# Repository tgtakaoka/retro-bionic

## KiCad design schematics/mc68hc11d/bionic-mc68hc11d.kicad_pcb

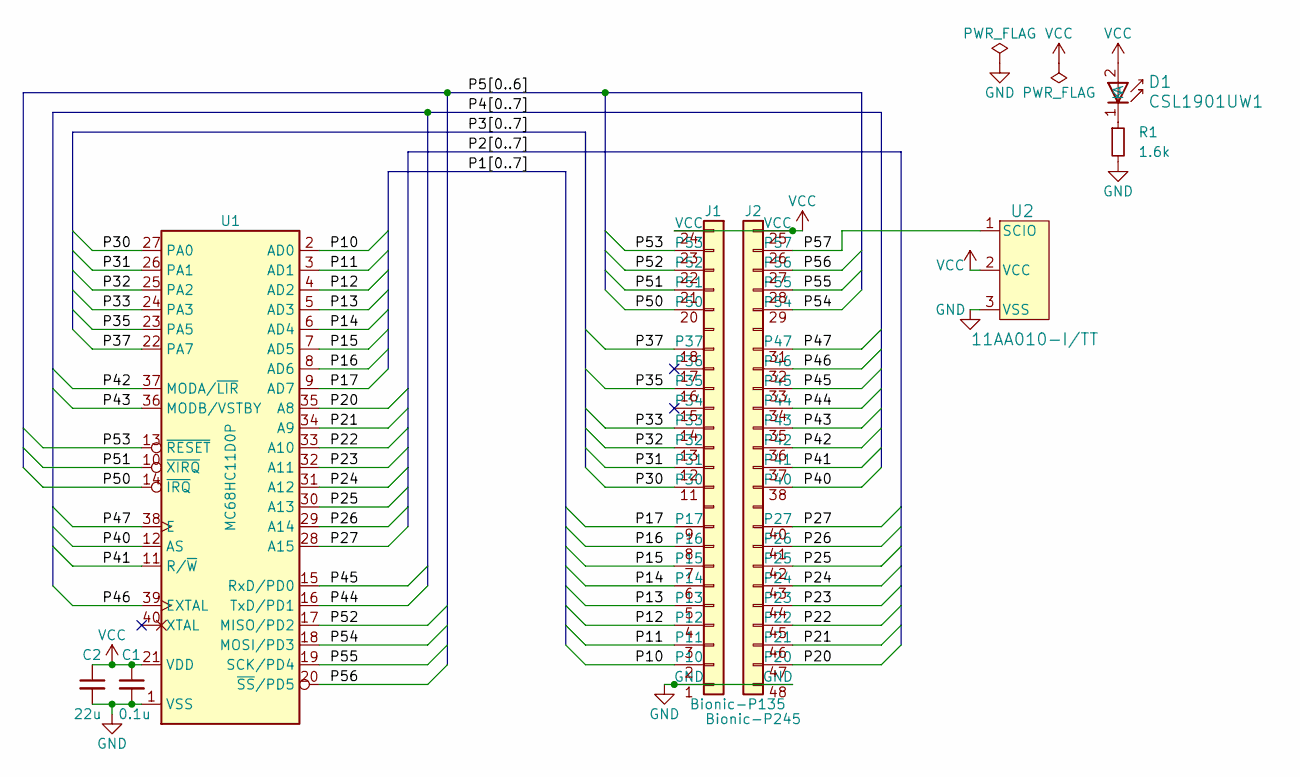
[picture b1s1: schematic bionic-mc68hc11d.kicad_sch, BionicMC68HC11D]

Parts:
C1: 0.1u; C_0603_1608Metric_Pad1.08x0.95mm_HandSolder
C2: 22u; C_0603_1608Metric_Pad1.08x0.95mm_HandSolder
D1: CSL1901UW1; LED_CSL1901UW1_ROM-M
J1: Bionic-P135; Bionic-P135_THT
J2: Bionic-P245; Bionic-P245_THT
R1: 1.6k; R_0603_1608Metric_Pad0.98x0.95mm_HandSolder
U1: MC68HC11D0P; DIP-40_W15.24mm_Socket
U2: 11AA010-I/TT; SOT-23_MC_MCH-M

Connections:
/P10: J1.2 (P10), U1.2 (AD0)
/P11: J1.3 (P11), U1.3 (AD1)
/P12: J1.4 (P12), U1.4 (AD2)
/P13: J1.5 (P13), U1.5 (AD3)
/P14: J1.6 (P14), U1.6 (AD4)
/P15: J1.7 (P15), U1.7 (AD5)
/P16: J1.8 (P16), U1.8 (AD6)
/P17: J1.9 (P17), U1.9 (AD7)
/P20: J2.47 (P20), U1.35 (A8)
/P21: J2.46 (P21), U1.34 (A9)
/P22: J2.45 (P22), U1.33 (A10)
/P23: J2.44 (P23), U1.32 (A11)
/P24: J2.43 (P24), U1.31 (A12)
/P25: J2.42 (P25), U1.30 (A13)
/P26: J2.41 (P26), U1.29 (A14)
/P27: J2.40 (P27), U1.28 (A15)
/P30: J1.11 (P30), U1.27 (PA0)
/P31: J1.12 (P31), U1.26 (PA1)
/P32: J1.13 (P32), U1.25 (PA2)
/P33: J1.14 (P33), U1.24 (PA3)
/P35: J1.16 (P35), U1.23 (PA5)
/P37: J1.18 (P37), U1.22 (PA7)
/P40: J2.38 (P40), U1.12 (AS)
/P41: J2.37 (P41), U1.11 (R/~W)
/P42: J2.36 (P42), U1.37 (MODA/~LIR)
/P43: J2.35 (P43), U1.36 (MODB/VSTBY)
/P44: J2.34 (P44), U1.16 (TxD/PD1)
/P45: J2.33 (P45), U1.15 (RxD/PD0)
/P46: J2.32 (P46), U1.39 (EXTAL)
/P47: J2.31 (P47), U1.38 (E)
/P50: J1.20 (P50), U1.14 (~IRQ)
/P51: J1.21 (P51), U1.10 (~XIRQ)
/P52: J1.22 (P52), U1.17 (MISO/PD2)
/P53: J1.23 (P53), U1.13 (~RESET)
/P54: J2.29 (P54), U1.18 (MOSI/PD3)
/P55: J2.28 (P55), U1.19 (SCK/PD4)
/P56: J2.27 (P56), U1.20 (~SS/PD5)
/P57: J2.26 (P57), U2.1 (SCIO)
GND: C1.2, C2.2, J1.1 (GND), J2.48 (GND), R1.2, U1.1 (VSS), U2.3 (VSS)
unnamed: D1.1 (K), R1.1
VCC: C1.1, C2.1, D1.2 (A), J1.24 (VCC), J2.25 (VCC), U1.21 (VDD), U2.2 (VCC)

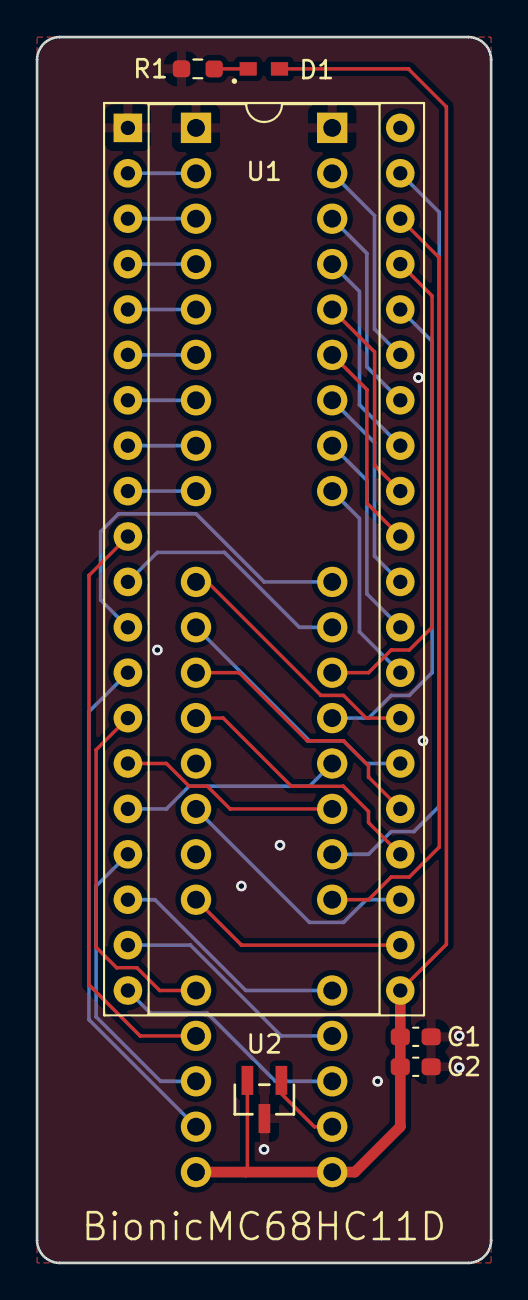
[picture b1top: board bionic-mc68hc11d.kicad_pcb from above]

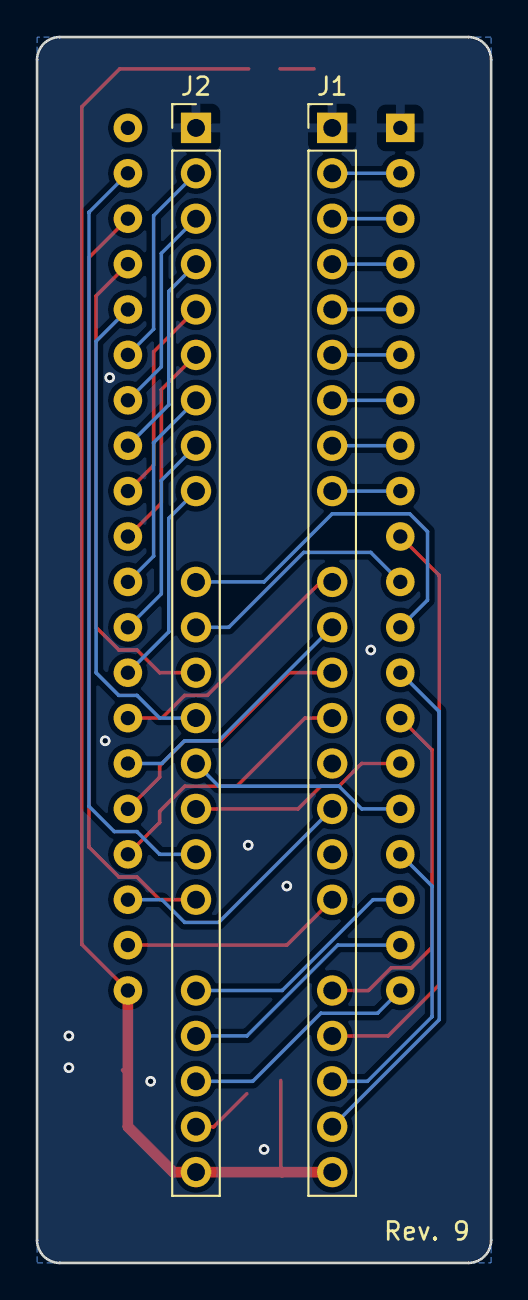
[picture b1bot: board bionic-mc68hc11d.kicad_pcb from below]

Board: 2 copper layers, 25.4 x 68.6 mm, 8 parts (2 on the bottom side), 41 nets.

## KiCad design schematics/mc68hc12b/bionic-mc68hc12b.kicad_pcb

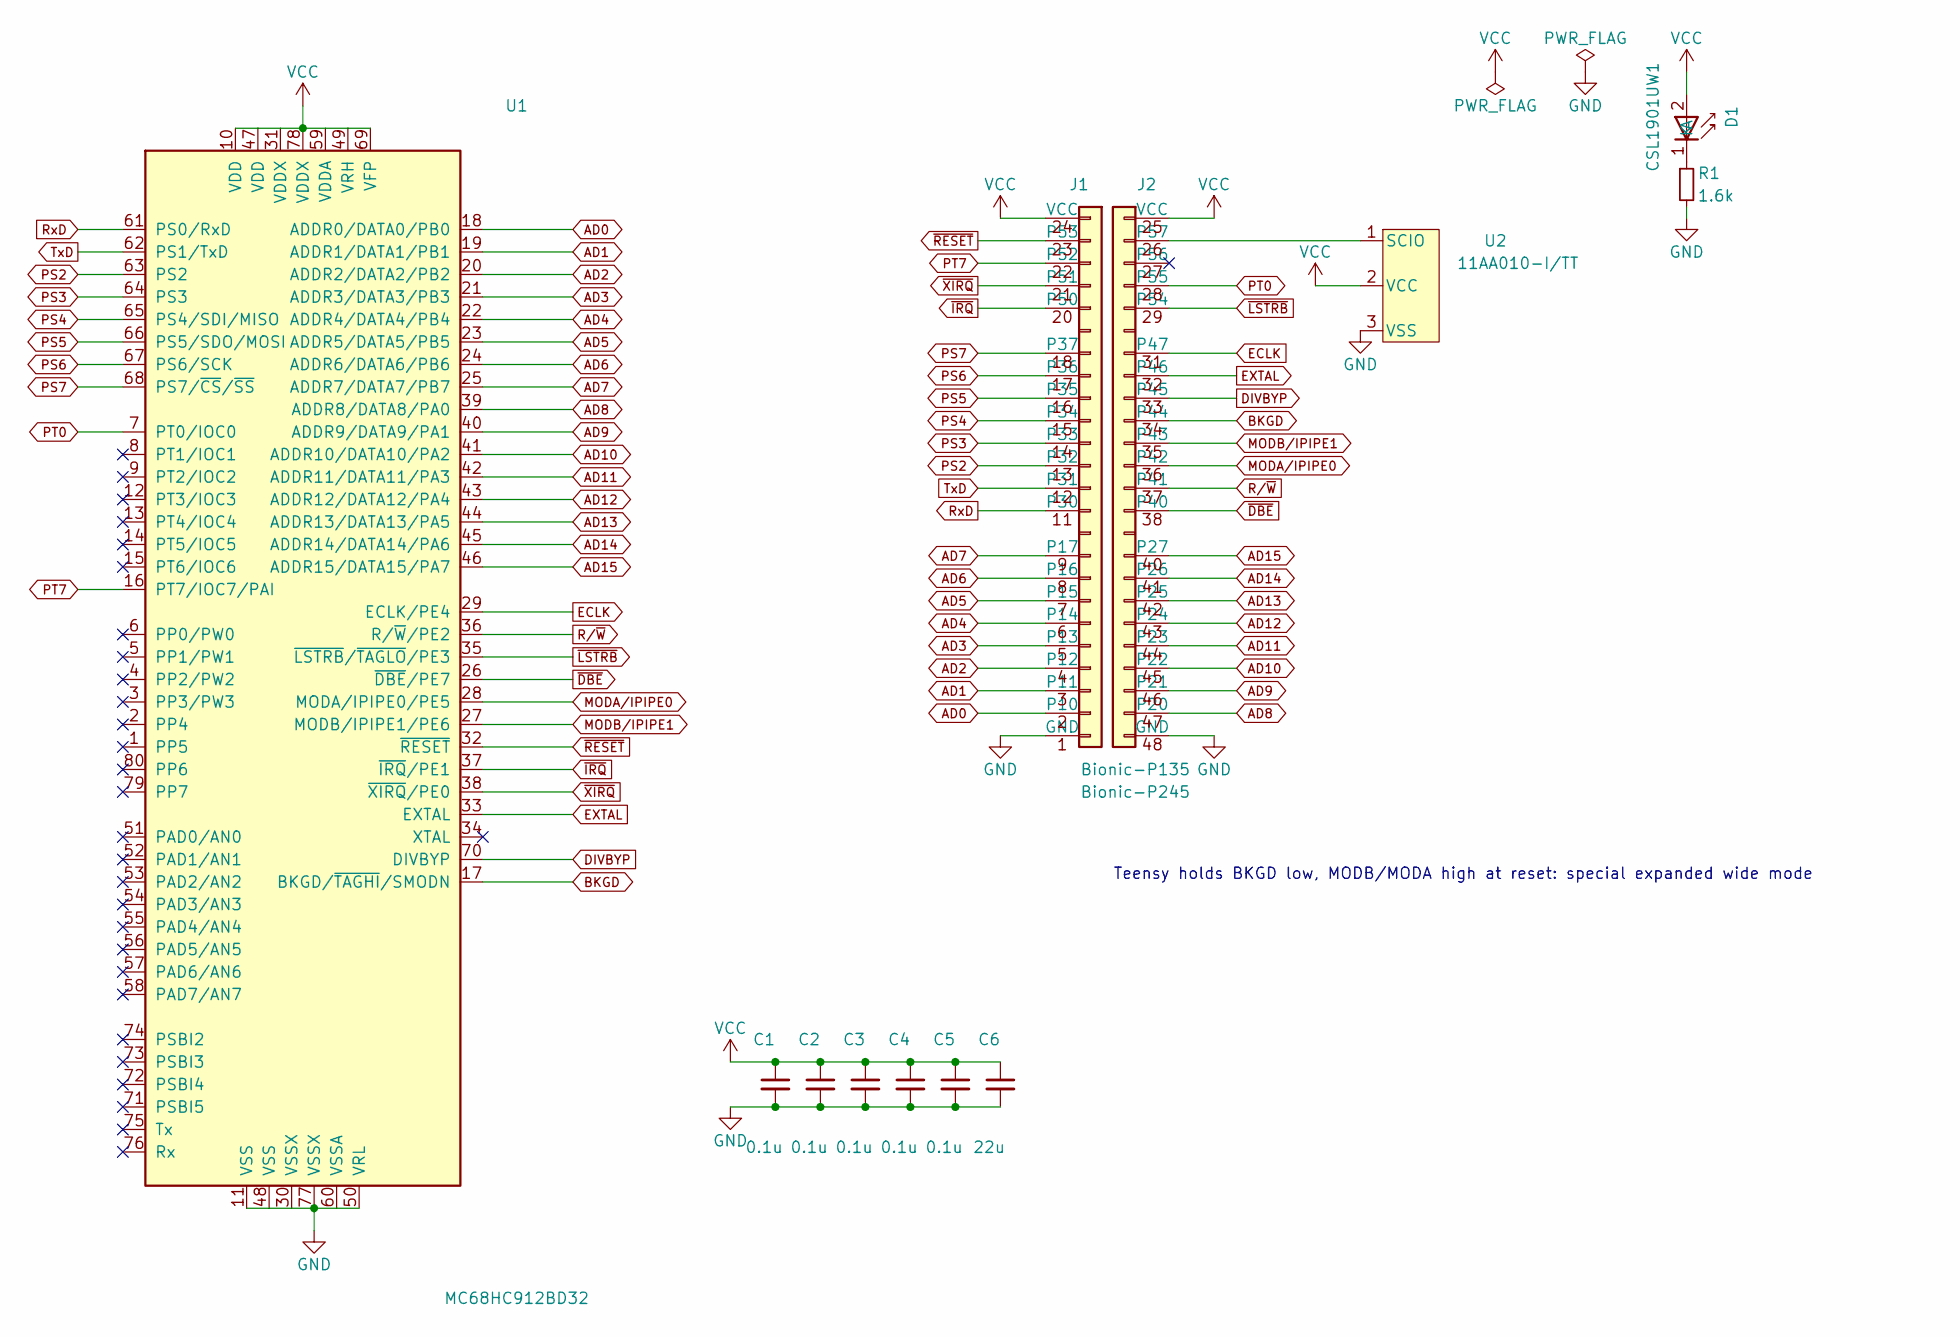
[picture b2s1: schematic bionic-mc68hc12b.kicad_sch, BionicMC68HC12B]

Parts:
C1, C2, C3, C4, C5: 0.1u; C_0603_1608Metric_Pad1.08x0.95mm_HandSolder
C6: 22u; C_0603_1608Metric_Pad1.08x0.95mm_HandSolder
D1: CSL1901UW1; LED_CSL1901UW1_ROM-M
J1: Bionic-P135; Bionic-P135_SMT
J2: Bionic-P245; Bionic-P245_SMT
R1: 1.6k; R_0603_1608Metric_Pad0.98x0.95mm_HandSolder
U1: MC68HC912BD32; PQFP-80_14x14mm_P0.65mm
U2: 11AA010-I/TT; SOT-23_MC_MCH-M

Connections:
AD0: J1.2 (P10), U1.18 (ADDR0/DATA0/PB0)
AD1: J1.3 (P11), U1.19 (ADDR1/DATA1/PB1)
AD2: J1.4 (P12), U1.20 (ADDR2/DATA2/PB2)
AD3: J1.5 (P13), U1.21 (ADDR3/DATA3/PB3)
AD4: J1.6 (P14), U1.22 (ADDR4/DATA4/PB4)
AD5: J1.7 (P15), U1.23 (ADDR5/DATA5/PB5)
AD6: J1.8 (P16), U1.24 (ADDR6/DATA6/PB6)
AD7: J1.9 (P17), U1.25 (ADDR7/DATA7/PB7)
AD8: J2.47 (P20), U1.39 (ADDR8/DATA8/PA0)
AD9: J2.46 (P21), U1.40 (ADDR9/DATA9/PA1)
AD10: J2.45 (P22), U1.41 (ADDR10/DATA10/PA2)
AD11: J2.44 (P23), U1.42 (ADDR11/DATA11/PA3)
AD12: J2.43 (P24), U1.43 (ADDR12/DATA12/PA4)
AD13: J2.42 (P25), U1.44 (ADDR13/DATA13/PA5)
AD14: J2.41 (P26), U1.45 (ADDR14/DATA14/PA6)
AD15: J2.40 (P27), U1.46 (ADDR15/DATA15/PA7)
BKGD: J2.34 (P44), U1.17 (BKGD/~TAGHI/SMODN)
DIVBYP: J2.33 (P45), U1.70 (DIVBYP)
ECLK: J2.31 (P47), U1.29 (ECLK/PE4)
EXTAL: J2.32 (P46), U1.33 (EXTAL)
GND: C1.2, C2.2, C3.2, C4.2, C5.2, C6.2, J1.1 (GND), J2.48 (GND), R1.2, U1.11 (VSS), U1.30 (VSSX), U1.48 (VSS), U1.50 (VRL), U1.60 (VSSA), U1.77 (VSSX), U2.3 (VSS)
MODA/IPIPE0: J2.36 (P42), U1.28 (MODA/IPIPE0/PE5)
MODB/IPIPE1: J2.35 (P43), U1.27 (MODB/IPIPE1/PE6)
unnamed: D1.1 (K), R1.1
unnamed: J2.26 (P57), U2.1 (SCIO)
PS2: J1.13 (P32), U1.63 (PS2)
PS3: J1.14 (P33), U1.64 (PS3)
PS4: J1.15 (P34), U1.65 (PS4/SDI/MISO)
PS5: J1.16 (P35), U1.66 (PS5/SDO/MOSI)
PS6: J1.17 (P36), U1.67 (PS6/SCK)
PS7: J1.18 (P37), U1.68 (PS7/~CS/~SS)
PT0: J2.28 (P55), U1.7 (PT0/IOC0)
PT7: J1.22 (P52), U1.16 (PT7/IOC7/PAI)
RxD: J1.11 (P30), U1.61 (PS0/RxD)
R/~W: J2.37 (P41), U1.36 (R/~W/PE2)
TxD: J1.12 (P31), U1.62 (PS1/TxD)
VCC: C1.1, C2.1, C3.1, C4.1, C5.1, C6.1, D1.2 (A), J1.24 (VCC), J2.25 (VCC), U1.10 (VDD), U1.31 (VDDX), U1.47 (VDD), U1.49 (VRH), U1.59 (VDDA), U1.69 (VFP), U1.78 (VDDX), U2.2 (VCC)
~DBE: J2.38 (P40), U1.26 (~DBE/PE7)
~IRQ: J1.20 (P50), U1.37 (~IRQ/PE1)
~LSTRB: J2.29 (P54), U1.35 (~LSTRB/~TAGLO/PE3)
~RESET: J1.23 (P53), U1.32 (~RESET)
~XIRQ: J1.21 (P51), U1.38 (~XIRQ/PE0)

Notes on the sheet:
Teensy holds BKGD low, MODB/MODA high at reset: special expanded wide mode

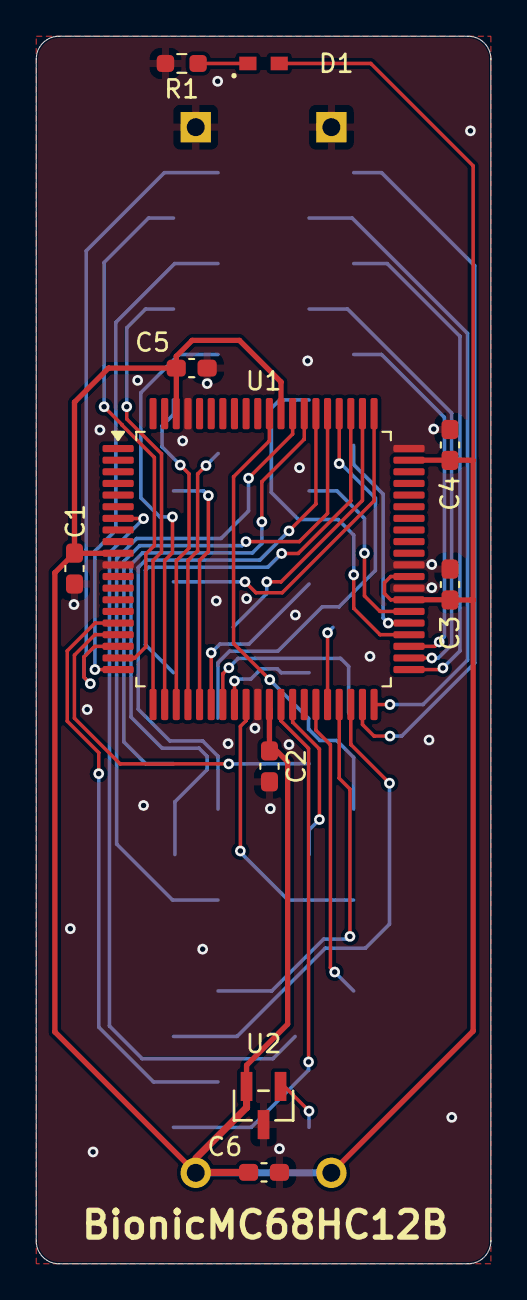
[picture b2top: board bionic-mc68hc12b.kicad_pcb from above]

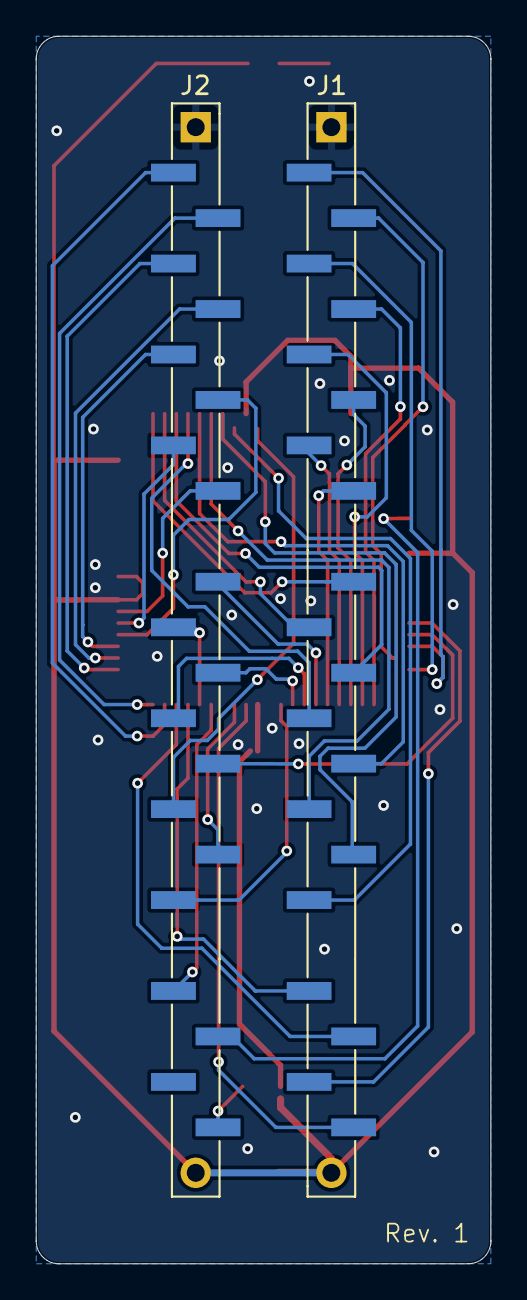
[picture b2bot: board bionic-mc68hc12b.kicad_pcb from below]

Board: 2 copper layers, 25.4 x 68.6 mm, 12 parts (2 on the bottom side), 42 nets.

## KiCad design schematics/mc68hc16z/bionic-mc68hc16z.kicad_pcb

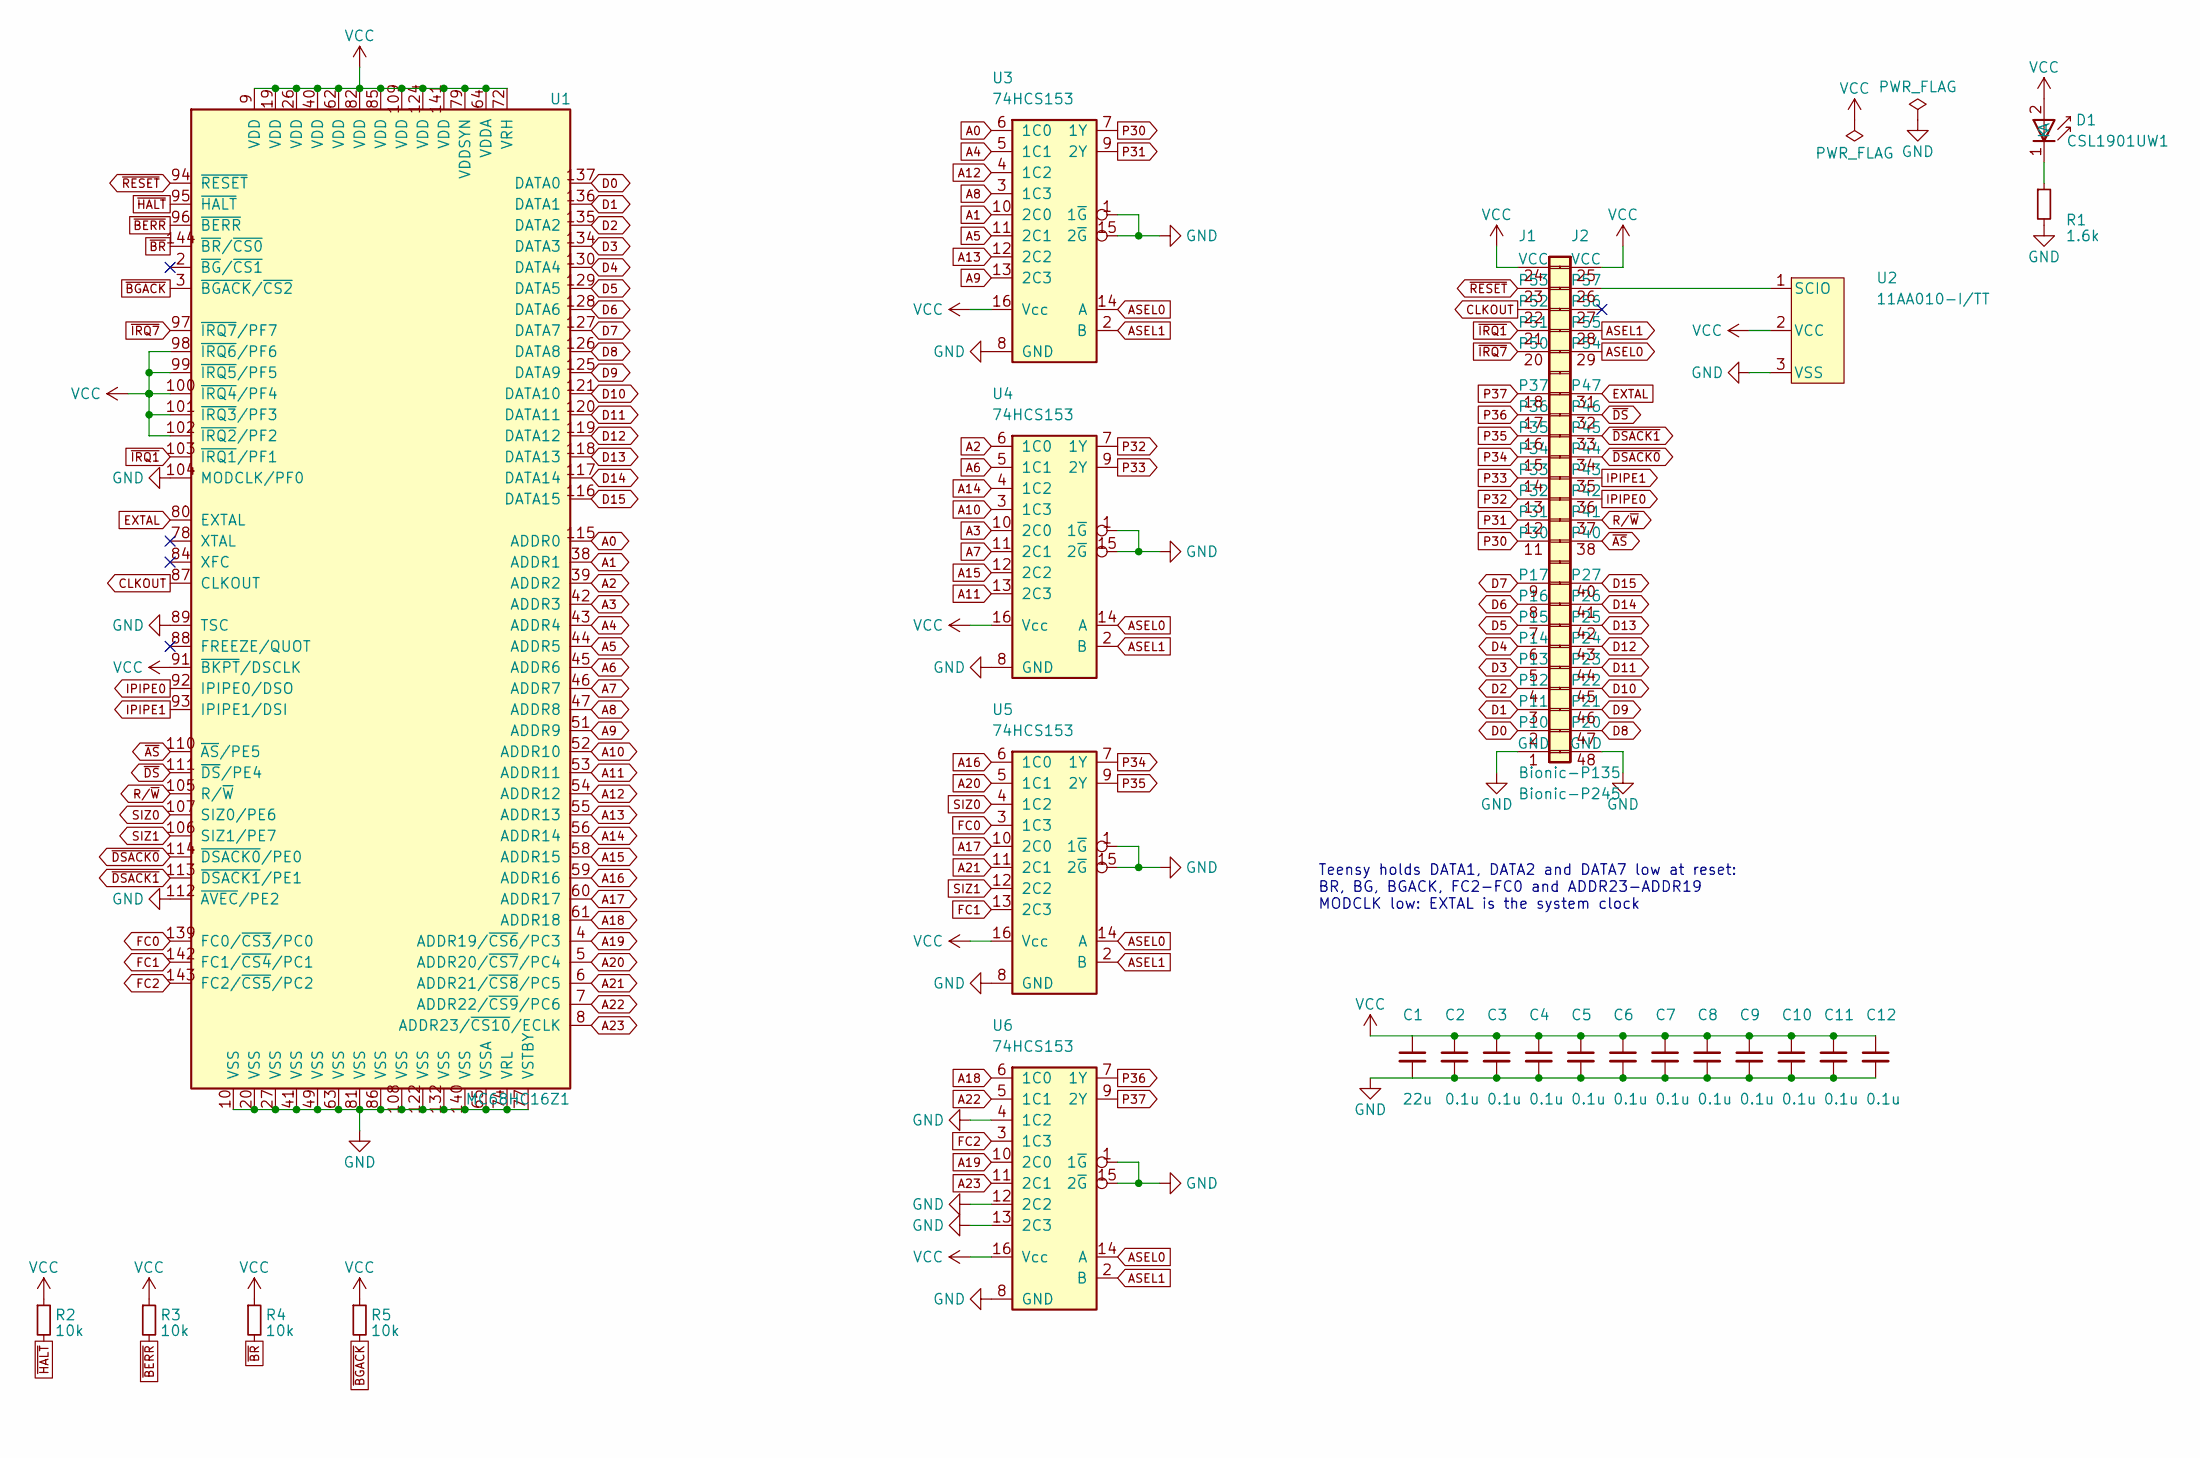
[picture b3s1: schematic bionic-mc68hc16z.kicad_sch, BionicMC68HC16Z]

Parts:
C1: 22u; C_0603_1608Metric_Pad1.08x0.95mm_HandSolder
C2, C3, C4, C5, C6, C7, C8, C9, C10, C11, C12: 0.1u; C_0603_1608Metric_Pad1.08x0.95mm_HandSolder
D1: CSL1901UW1; LED_CSL1901UW1_ROM-M
J1: Bionic-P135; Bionic-P135_SMT
J2: Bionic-P245; Bionic-P245_SMT
R1: 1.6k; R_0603_1608Metric_Pad0.98x0.95mm_HandSolder
R2, R3, R4, R5: 10k; R_0603_1608Metric_Pad0.98x0.95mm_HandSolder
U1: MC68HC16Z1; LQFP-144_20x20mm_P0.5mm
U2: 11AA010-I/TT; SOT-23_MC_MCH-M
U3, U4, U5, U6: 74HCS153; PW16-M

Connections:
A0: U1.115 (ADDR0), U3.6 (1C0)
A1: U1.38 (ADDR1), U3.10 (2C0)
A2: U1.39 (ADDR2), U4.6 (1C0)
A3: U1.42 (ADDR3), U4.10 (2C0)
A4: U1.43 (ADDR4), U3.5 (1C1)
A5: U1.44 (ADDR5), U3.11 (2C1)
A6: U1.45 (ADDR6), U4.5 (1C1)
A7: U1.46 (ADDR7), U4.11 (2C1)
A8: U1.47 (ADDR8), U3.3 (1C3)
A9: U1.51 (ADDR9), U3.13 (2C3)
A10: U1.52 (ADDR10), U4.3 (1C3)
A11: U1.53 (ADDR11), U4.13 (2C3)
A12: U1.54 (ADDR12), U3.4 (1C2)
A13: U1.55 (ADDR13), U3.12 (2C2)
A14: U1.56 (ADDR14), U4.4 (1C2)
A15: U1.58 (ADDR15), U4.12 (2C2)
A16: U1.59 (ADDR16), U5.6 (1C0)
A17: U1.60 (ADDR17), U5.10 (2C0)
A18: U1.61 (ADDR18), U6.6 (1C0)
A19: U1.4 (ADDR19/~CS6/PC3), U6.10 (2C0)
A20: U1.5 (ADDR20/~CS7/PC4), U5.5 (1C1)
A21: U1.6 (ADDR21/~CS8/PC5), U5.11 (2C1)
A22: U1.7 (ADDR22/~CS9/PC6), U6.5 (1C1)
A23: U1.8 (ADDR23/~CS10/ECLK), U6.11 (2C1)
ASEL0: J2.29 (P54), U3.14 (A), U4.14 (A), U5.14 (A), U6.14 (A)
ASEL1: J2.28 (P55), U3.2 (B), U4.2 (B), U5.2 (B), U6.2 (B)
CLKOUT: J1.22 (P52), U1.87 (CLKOUT)
D0: J1.2 (P10), U1.137 (DATA0)
D1: J1.3 (P11), U1.136 (DATA1)
D2: J1.4 (P12), U1.135 (DATA2)
D3: J1.5 (P13), U1.134 (DATA3)
D4: J1.6 (P14), U1.130 (DATA4)
D5: J1.7 (P15), U1.129 (DATA5)
D6: J1.8 (P16), U1.128 (DATA6)
D7: J1.9 (P17), U1.127 (DATA7)
D8: J2.47 (P20), U1.126 (DATA8)
D9: J2.46 (P21), U1.125 (DATA9)
D10: J2.45 (P22), U1.121 (DATA10)
D11: J2.44 (P23), U1.120 (DATA11)
D12: J2.43 (P24), U1.119 (DATA12)
D13: J2.42 (P25), U1.118 (DATA13)
D14: J2.41 (P26), U1.117 (DATA14)
D15: J2.40 (P27), U1.116 (DATA15)
EXTAL: J2.31 (P47), U1.80 (EXTAL)
FC0: U1.139 (FC0/~CS3/PC0), U5.3 (1C3)
FC1: U1.142 (FC1/~CS4/PC1), U5.13 (2C3)
FC2: U1.143 (FC2/~CS5/PC2), U6.3 (1C3)
GND: C1.2, C2.2, C3.2, C4.2, C5.2, C6.2, C7.2, C8.2, C9.2, C10.2, C11.2, C12.2, J1.1 (GND), J2.48 (GND), R1.2, U1.10 (VSS), U1.20 (VSS), U1.27 (VSS), U1.41 (VSS), U1.49 (VSS), U1.63 (VSS), U1.65 (VSSA), U1.74 (VRL), U1.77 (VSTBY), U1.81 (VSS), U1.86 (VSS), U1.89 (TSC), U1.104 (MODCLK/PF0), U1.108 (VSS), U1.112 (~AVEC/PE2), U1.122 (VSS), U1.132 (VSS), U1.140 (VSS), U2.3 (VSS), U3.1 (1~G), U3.8 (GND), U3.15 (2~G), U4.1 (1~G), U4.8 (GND), U4.15 (2~G), U5.1 (1~G), U5.8 (GND), U5.15 (2~G), U6.1 (1~G), U6.4 (1C2), U6.8 (GND), U6.12 (2C2), U6.13 (2C3), U6.15 (2~G)
IPIPE0: J2.36 (P42), U1.92 (IPIPE0/DSO)
IPIPE1: J2.35 (P43), U1.93 (IPIPE1/DSI)
unnamed: D1.1 (K), R1.1
unnamed: J2.26 (P57), U2.1 (SCIO)
P30: J1.11 (P30), U3.7 (1Y)
P31: J1.12 (P31), U3.9 (2Y)
P32: J1.13 (P32), U4.7 (1Y)
P33: J1.14 (P33), U4.9 (2Y)
P34: J1.15 (P34), U5.7 (1Y)
P35: J1.16 (P35), U5.9 (2Y)
P36: J1.17 (P36), U6.7 (1Y)
P37: J1.18 (P37), U6.9 (2Y)
R/~W: J2.37 (P41), U1.105 (R/~W)
SIZ0: U1.107 (SIZ0/PE6), U5.4 (1C2)
SIZ1: U1.106 (SIZ1/PE7), U5.12 (2C2)
VCC: C1.1, C2.1, C3.1, C4.1, C5.1, C6.1, C7.1, C8.1, C9.1, C10.1, C11.1, C12.1, D1.2 (A), J1.24 (VCC), J2.25 (VCC), R2.1, R3.1, R4.1, R5.1, U1.9 (VDD), U1.19 (VDD), U1.26 (VDD), U1.40 (VDD), U1.62 (VDD), U1.64 (VDDA), U1.72 (VRH), U1.79 (VDDSYN), U1.82 (VDD), U1.85 (VDD), U1.91 (~BKPT/DSCLK), U1.98 (~IRQ6/PF6), U1.99 (~IRQ5/PF5), U1.100 (~IRQ4/PF4), U1.101 (~IRQ3/PF3), U1.102 (~IRQ2/PF2), U1.109 (VDD), U1.124 (VDD), U1.141 (VDD), U2.2 (VCC), U3.16 (Vcc), U4.16 (Vcc), U5.16 (Vcc), U6.16 (Vcc)
~AS: J2.38 (P40), U1.110 (~AS/PE5)
~BERR: R3.2, U1.96 (~BERR)
~BGACK: R5.2, U1.3 (~BGACK/~CS2)
~BR: R4.2, U1.144 (~BR/~CS0)
~DSACK0: J2.34 (P44), U1.114 (~DSACK0/PE0)
~DSACK1: J2.33 (P45), U1.113 (~DSACK1/PE1)
~DS: J2.32 (P46), U1.111 (~DS/PE4)
~HALT: R2.2, U1.95 (~HALT)
~IRQ1: J1.21 (P51), U1.103 (~IRQ1/PF1)
~IRQ7: J1.20 (P50), U1.97 (~IRQ7/PF7)
~RESET: J1.23 (P53), U1.94 (~RESET)

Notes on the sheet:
Teensy holds DATA1, DATA2 and DATA7 low at reset: BR, BG, BGACK, FC2-FC0 and ADDR23-ADDR19 MODCLK low: EXTAL is the system clock

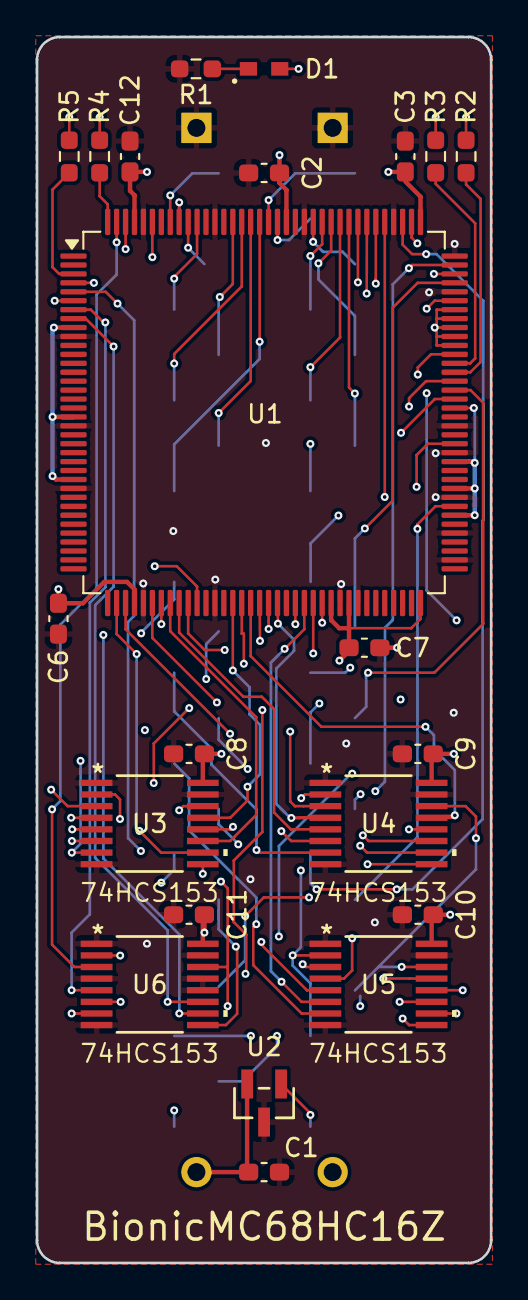
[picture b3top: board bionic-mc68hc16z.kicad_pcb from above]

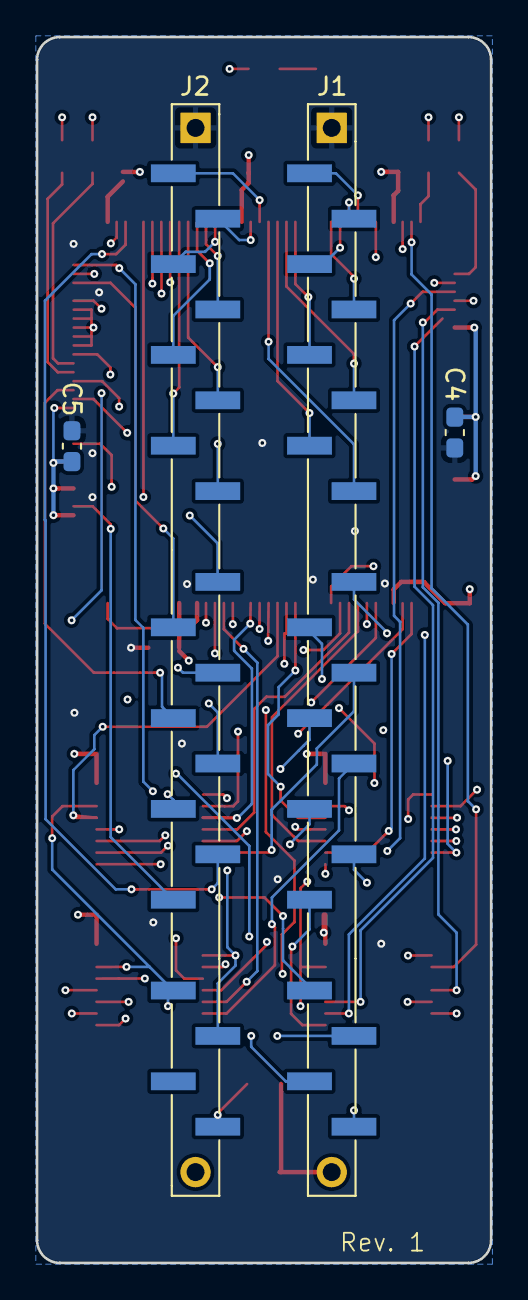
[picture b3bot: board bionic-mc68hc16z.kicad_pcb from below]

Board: 4 copper layers, 25.4 x 68.6 mm, 26 parts (4 on the bottom side), 75 nets.

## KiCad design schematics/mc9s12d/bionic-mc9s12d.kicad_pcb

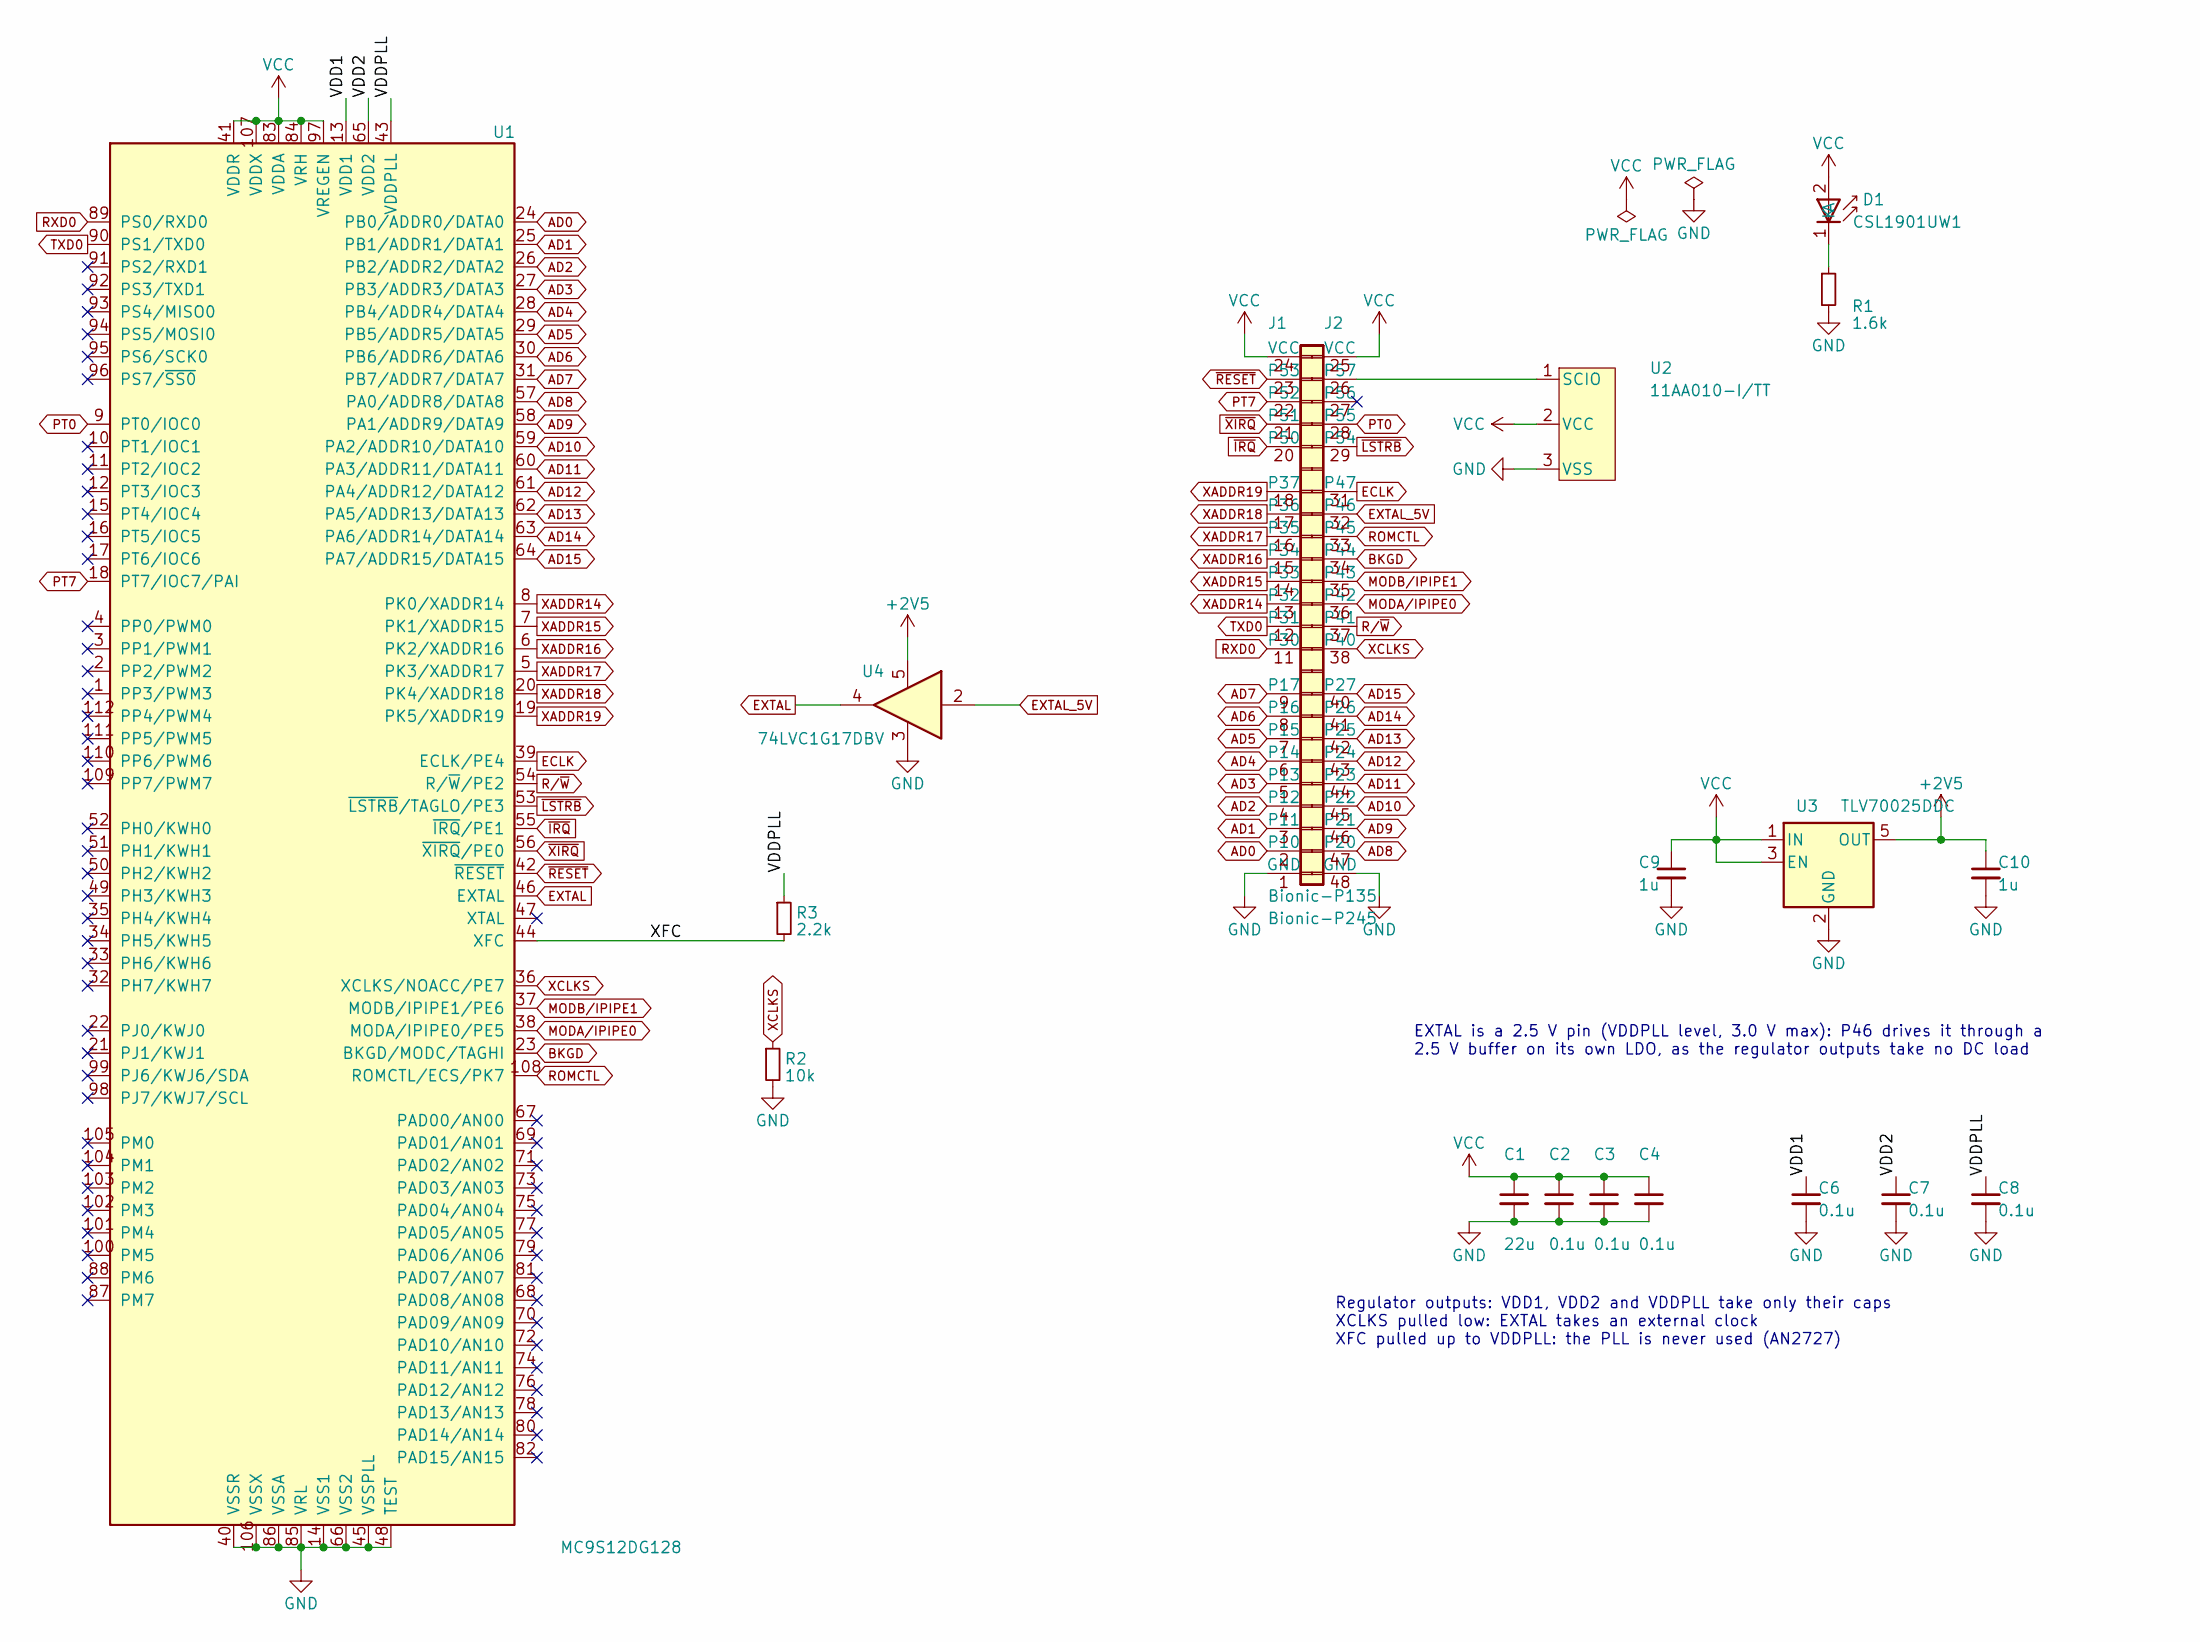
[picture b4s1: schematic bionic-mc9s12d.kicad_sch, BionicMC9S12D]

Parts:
C1: 22u; C_0603_1608Metric_Pad1.08x0.95mm_HandSolder
C2, C3, C4, C6, C7, C8: 0.1u; C_0603_1608Metric_Pad1.08x0.95mm_HandSolder
C9, C10: 1u; C_0603_1608Metric_Pad1.08x0.95mm_HandSolder
D1: CSL1901UW1; LED_CSL1901UW1_ROM-M
J1: Bionic-P135; Bionic-P135_SMT
J2: Bionic-P245; Bionic-P245_SMT
R1: 1.6k; R_0603_1608Metric_Pad0.98x0.95mm_HandSolder
R2: 10k; R_0603_1608Metric_Pad0.98x0.95mm_HandSolder
R3: 2.2k; R_0603_1608Metric_Pad0.98x0.95mm_HandSolder
U1: MC9S12DG128; LQFP-112_20x20mm_P0.65mm
U2: 11AA010-I/TT; SOT-23_MC_MCH-M
U3: TLV70025DDC; DBV5-M
U4: 74LVC1G17DBV; DBV5-M

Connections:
+2V5: C10.1, U3.5 (OUT), U4.5 (VCC)
/VDD1: C6.1, U1.13 (VDD1)
/VDD2: C7.1, U1.65 (VDD2)
/VDDPLL: C8.1, R3.1, U1.43 (VDDPLL)
/XFC: R3.2, U1.44 (XFC)
AD0: J1.2 (P10), U1.24 (PB0/ADDR0/DATA0)
AD1: J1.3 (P11), U1.25 (PB1/ADDR1/DATA1)
AD2: J1.4 (P12), U1.26 (PB2/ADDR2/DATA2)
AD3: J1.5 (P13), U1.27 (PB3/ADDR3/DATA3)
AD4: J1.6 (P14), U1.28 (PB4/ADDR4/DATA4)
AD5: J1.7 (P15), U1.29 (PB5/ADDR5/DATA5)
AD6: J1.8 (P16), U1.30 (PB6/ADDR6/DATA6)
AD7: J1.9 (P17), U1.31 (PB7/ADDR7/DATA7)
AD8: J2.47 (P20), U1.57 (PA0/ADDR8/DATA8)
AD9: J2.46 (P21), U1.58 (PA1/ADDR9/DATA9)
AD10: J2.45 (P22), U1.59 (PA2/ADDR10/DATA10)
AD11: J2.44 (P23), U1.60 (PA3/ADDR11/DATA11)
AD12: J2.43 (P24), U1.61 (PA4/ADDR12/DATA12)
AD13: J2.42 (P25), U1.62 (PA5/ADDR13/DATA13)
AD14: J2.41 (P26), U1.63 (PA6/ADDR14/DATA14)
AD15: J2.40 (P27), U1.64 (PA7/ADDR15/DATA15)
BKGD: J2.34 (P44), U1.23 (BKGD/MODC/TAGHI)
ECLK: J2.31 (P47), U1.39 (ECLK/PE4)
EXTAL: U1.46 (EXTAL), U4.4 (Y)
EXTAL_5V: J2.32 (P46), U4.2 (A)
GND: C1.2, C2.2, C3.2, C4.2, C6.2, C7.2, C8.2, C9.2, C10.2, J1.1 (GND), J2.48 (GND), R1.2, R2.2, U1.14 (VSS1), U1.40 (VSSR), U1.45 (VSSPLL), U1.48 (TEST), U1.66 (VSS2), U1.85 (VRL), U1.86 (VSSA), U1.106 (VSSX), U2.3 (VSS), U3.2 (GND), U4.3 (GND)
MODA/IPIPE0: J2.36 (P42), U1.38 (MODA/IPIPE0/PE5)
MODB/IPIPE1: J2.35 (P43), U1.37 (MODB/IPIPE1/PE6)
unnamed: D1.1 (K), R1.1
unnamed: J2.26 (P57), U2.1 (SCIO)
PT0: J2.28 (P55), U1.9 (PT0/IOC0)
PT7: J1.22 (P52), U1.18 (PT7/IOC7/PAI)
ROMCTL: J2.33 (P45), U1.108 (ROMCTL/ECS/PK7)
RXD0: J1.11 (P30), U1.89 (PS0/RXD0)
R/~W: J2.37 (P41), U1.54 (R/~W/PE2)
TXD0: J1.12 (P31), U1.90 (PS1/TXD0)
VCC: C1.1, C2.1, C3.1, C4.1, C9.1, D1.2 (A), J1.24 (VCC), J2.25 (VCC), U1.41 (VDDR), U1.83 (VDDA), U1.84 (VRH), U1.97 (VREGEN), U1.107 (VDDX), U2.2 (VCC), U3.1 (IN), U3.3 (EN)
XADDR14: J1.13 (P32), U1.8 (PK0/XADDR14)
XADDR15: J1.14 (P33), U1.7 (PK1/XADDR15)
XADDR16: J1.15 (P34), U1.6 (PK2/XADDR16)
XADDR17: J1.16 (P35), U1.5 (PK3/XADDR17)
XADDR18: J1.17 (P36), U1.20 (PK4/XADDR18)
XADDR19: J1.18 (P37), U1.19 (PK5/XADDR19)
XCLKS: J2.38 (P40), R2.1, U1.36 (XCLKS/NOACC/PE7)
~IRQ: J1.20 (P50), U1.55 (~IRQ/PE1)
~LSTRB: J2.29 (P54), U1.53 (~LSTRB/TAGLO/PE3)
~RESET: J1.23 (P53), U1.42 (~RESET)
~XIRQ: J1.21 (P51), U1.56 (~XIRQ/PE0)

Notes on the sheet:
EXTAL is a 2.5 V pin (VDDPLL level, 3.0 V max): P46 drives it through a 2.5 V buffer on its own LDO, as the regulator outputs take no DC load
Regulator outputs: VDD1, VDD2 and VDDPLL take only their caps XCLKS pulled low: EXTAL takes an external clock XFC pulled up to VDDPLL: the PLL is never used (AN2727)
